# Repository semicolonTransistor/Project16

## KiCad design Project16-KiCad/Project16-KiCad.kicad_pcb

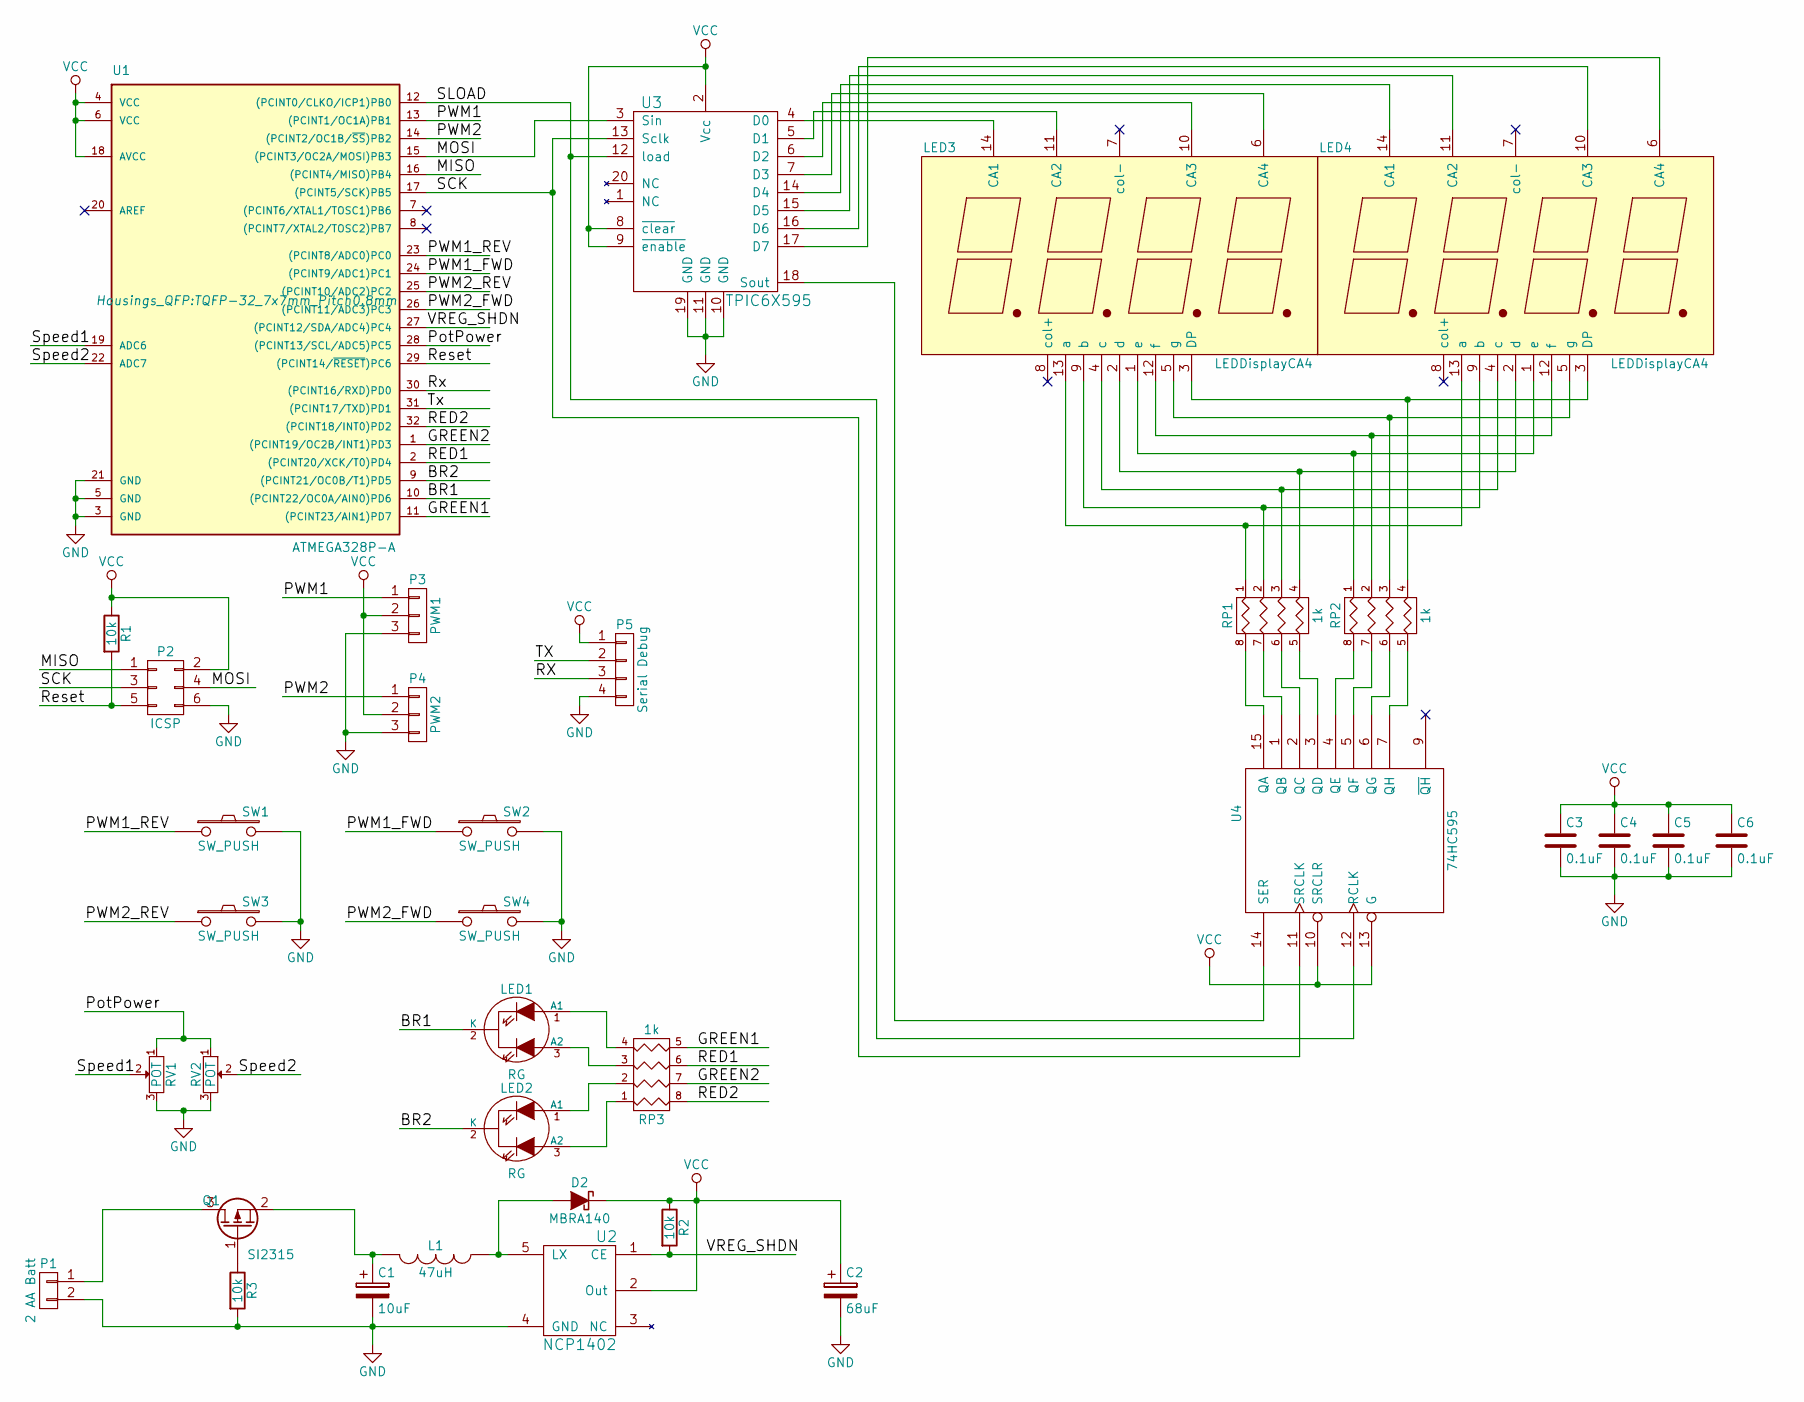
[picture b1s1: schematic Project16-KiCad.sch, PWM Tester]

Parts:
C1: 10uF; CP_Radial_D5.0mm_P2.00mm
C2: 68uF; CP_Radial_D6.3mm_P2.50mm
C3, C4, C5, C6: 0.1uF; C_1206_HandSoldering
D2: MBRA140; D_SMA_Handsoldering
L1: 47uH; Choke_Toroid_5x10mm_Vertical
LED1, LED2: RG; LED_D5.0mm-3
LED3, LED4: LEDDisplayCA4; 7SegLedDisp4Digit
P1: 2 AA Batt; Pin_Header_Straight_1x02_Pitch2.54mm
P2: ICSP; Pin_Header_Straight_2x03_Pitch2.54mm
P3: PWM1; Pin_Header_Angled_1x03_Pitch2.54mm
P4: PWM2; Pin_Header_Angled_1x03_Pitch2.54mm
P5: Serial Debug; Pin_Header_Straight_1x04_Pitch2.54mm
Q1: SI2315; SOT-23_Handsoldering
R1, R2, R3: 10k; R_1206_HandSoldering
RP1, RP2, RP3: 1k; R_Array_Convex_4x1206
RV1, RV2: POT; 45mmSlidePot
SW1, SW2, SW3, SW4: SW_PUSH; Btn12x12
U1: ATMEGA328P-A; TQFP-32_7x7mm_Pitch0.8mm
U2: NCP1402; SOT-23-5_HandSoldering
U3: TPIC6X595; SOIC-20W_7.5x12.8mm_Pitch1.27mm
U4: 74HC595; SOIC-16_3.9x9.9mm_Pitch1.27mm

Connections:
/BR1: LED1.2 (K), U1.10 ((PCINT22/OC0A/AIN0)PD6)
/BR2: LED2.2 (K), U1.9 ((PCINT21/OC0B/T1)PD5)
/GREEN1: RP3.5 (R4), U1.11 ((PCINT23/AIN1)PD7)
/GREEN2: RP3.7 (R2), U1.1 ((PCINT19/OC2B/INT1)PD3)
/MISO: P2.1, U1.16 ((PCINT4/MISO)PB4)
/MOSI: P2.4, U1.15 ((PCINT3/OC2A/MOSI)PB3), U3.3 (Sin)
/PWM1: P3.1, U1.13 ((PCINT1/OC1A)PB1)
/PWM1_FWD: SW2.1, U1.24 ((PCINT9/ADC1)PC1)
/PWM1_REV: SW1.1, U1.23 ((PCINT8/ADC0)PC0)
/PWM2: P4.1, U1.14 ((PCINT2/OC1B/~SS~)PB2)
/PWM2_FWD: SW4.1, U1.26 ((PCINT11/ADC3)PC3)
/PWM2_REV: SW3.1, U1.25 ((PCINT10/ADC2)PC2)
/PotPower: RV1.1, RV2.1, U1.28 ((PCINT13/SCL/ADC5)PC5)
/RED1: RP3.6 (R3), U1.2 ((PCINT20/XCK/T0)PD4)
/RED2: RP3.8 (R1), U1.32 ((PCINT18/INT0)PD2)
/RX: P5.3, U1.30 ((PCINT16/RXD)PD0)
/Reset: P2.5, R1.2, U1.29 ((PCINT14/~RESET~)PC6)
/SCK: P2.3, U1.17 ((PCINT5/SCK)PB5), U3.13 (Sclk), U4.11 (SRCLK)
/SLOAD: U1.12 ((PCINT0/CLKO/ICP1)PB0), U3.12 (load), U4.12 (RCLK)
/Speed1: RV1.2, U1.19 (ADC6)
/Speed2: RV2.2, U1.22 (ADC7)
/TX: P5.2, U1.31 ((PCINT17/TXD)PD1)
/VREG_SHDN: R2.2, U1.27 ((PCINT12/SDA/ADC4)PC4), U2.1 (CE)
GND: C1.2, C2.2, C3.2, C4.2, C5.2, C6.2, P1.2, P2.6, P3.3, P4.3, P5.4, R3.2, RV1.3, RV2.3, SW1.2, SW2.2, SW3.2, SW4.2, U1.3 (GND), U1.5 (GND), U1.21 (GND), U2.4 (GND), U3.10 (GND), U3.11 (GND), U3.19 (GND), U4.8 (GND)
unnamed: C1.1, L1.2, Q1.2 (S)
unnamed: D2.2 (A), L1.1, U2.5 (LX)
unnamed: LED1.1 (A1), RP3.4
unnamed: LED1.3 (A2), RP3.3
unnamed: LED2.1 (A1), RP3.2
unnamed: LED2.3 (A2), RP3.1
unnamed: LED3.1 (e), LED4.1 (e), RP2.1
unnamed: LED3.2 (d), LED4.2 (d), RP1.4
unnamed: LED3.3 (DP), LED4.3 (DP), RP2.4
unnamed: LED3.4 (c), LED4.4 (c), RP1.3
unnamed: LED3.5 (g), LED4.5 (g), RP2.3
unnamed: LED3.6 (CA4), U3.7 (D3)
unnamed: LED3.9 (b), LED4.9 (b), RP1.2
unnamed: LED3.10 (CA3), U3.6 (D2)
unnamed: LED3.11 (CA2), U3.5 (D1)
unnamed: LED3.12 (f), LED4.12 (f), RP2.2
unnamed: LED3.13 (a), LED4.13 (a), RP1.1
unnamed: LED3.14 (CA1), U3.4 (D0)
unnamed: LED4.6 (CA4), U3.17 (D7)
unnamed: LED4.10 (CA3), U3.16 (D6)
unnamed: LED4.11 (CA2), U3.15 (D5)
unnamed: LED4.14 (CA1), U3.14 (D4)
unnamed: P1.1, Q1.3 (D)
unnamed: Q1.1 (G), R3.1
unnamed: RP1.5 (R4), U4.3 (QD)
unnamed: RP1.6 (R3), U4.2 (QC)
unnamed: RP1.7 (R2), U4.1 (QB)
unnamed: RP1.8 (R1), U4.15 (QA)
unnamed: RP2.5 (R4), U4.7 (QH)
unnamed: RP2.6 (R3), U4.6 (QG)
unnamed: RP2.7 (R2), U4.5 (QF)
unnamed: RP2.8 (R1), U4.4 (QE)
unnamed: U3.18 (Sout), U4.14 (SER)
VCC: C2.1, C3.1, C4.1, C5.1, C6.1, D2.1 (K), P2.2, P3.2, P4.2, P5.1, R1.1, R2.1, U1.4 (VCC), U1.6 (VCC), U1.18 (AVCC), U2.2 (Out), U3.2 (Vcc), U3.8 (~clear), U3.9 (~enable), U4.10 (SRCLR), U4.13 (G), U4.16 (VCC)

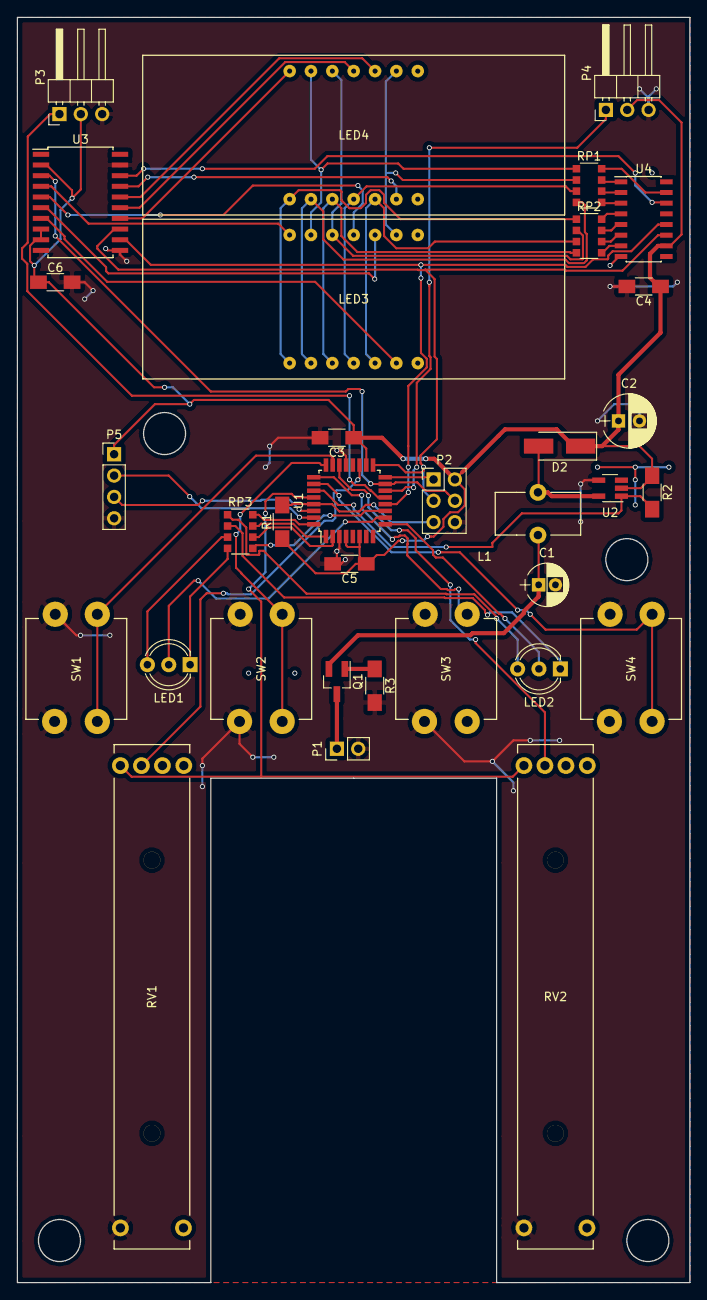
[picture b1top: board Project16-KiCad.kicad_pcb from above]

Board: 2 copper layers, 80.0 x 150.5 mm, 34 parts (0 on the bottom side), 58 nets.

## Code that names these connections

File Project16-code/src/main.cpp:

#include <Arduino.h>

#define GREEN1 7
#define RED1 4
#define BRIGHTNESS1 6

#define GREEN2 3
#define RED2 2
#define BRIGHTNESS2 5


void setup() {
  pinMode(BRIGHTNESS1,OUTPUT);
  pinMode(RED1, OUTPUT);
  pinMode(GREEN1, OUTPUT);
  digitalWrite(BRIGHTNESS1,LOW);
  pinMode(BRIGHTNESS2,OUTPUT);
  pinMode(RED2, OUTPUT);
  pinMode(GREEN2, OUTPUT);
  digitalWrite(BRIGHTNESS2,LOW);


}

void loop() {
  digitalWrite(RED1,LOW);
  digitalWrite(RED2,LOW);
  digitalWrite(GREEN1,HIGH);
  digitalWrite(GREEN2,HIGH);
  delay(1000);
  digitalWrite(RED1,HIGH);
  digitalWrite(RED2,HIGH);
  digitalWrite(GREEN1,LOW);
  digitalWrite(GREEN2,LOW);
  delay(1000);

}

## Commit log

2017-09-23 InitalCommit@rev0.2
2017-09-23 Completed footprint map for 0.2
2017-09-23 V0.3 Prototype
2017-11-08 Prototype 1.
2017-11-12 Improved boost converter, Added crystal.
2017-11-13 added lcd display
2017-11-14 Added License Statement, Minor circuit corrections
2017-11-14 Added License for hardware portion of the project
